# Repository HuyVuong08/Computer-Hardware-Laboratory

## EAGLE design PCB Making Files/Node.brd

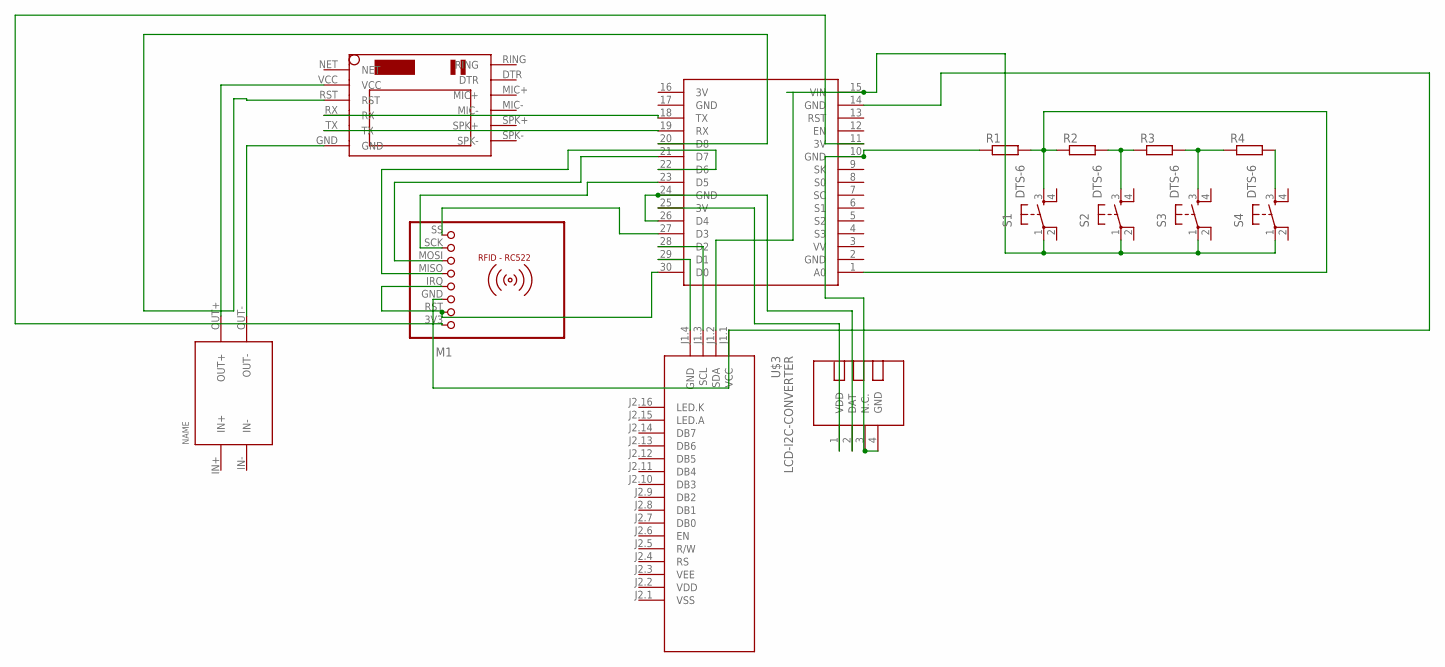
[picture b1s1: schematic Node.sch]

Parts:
M1: RFID-RC522
R1, R2, R3, R4: R-EU_0817/22; P0817/22
S1, S2, S3, S4: DTS-6
U$1: NODEMCU
U$2: TEMP-HUM-SENSOR-DHT11
U$3: LCD-I2C-CONVERTER
U$4: SIM800LMODULE
U$5: CP8-ADJ

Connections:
3V: U$1.16 (3V)
GND: U$1.2 (GND), U$1.17 (GND)
unnamed: U$4.GND, U$5.OUT-
unnamed: U$4.VCC, U$5.OUT+
unnamed: U$1.20 (D8), U$4.RST
unnamed: U$1.18 (TX), U$4.RX
unnamed: U$1.19 (RX), U$4.TX
unnamed: M1.MISO (5), U$1.22 (D6)
unnamed: M1.MOSI (6), U$1.21 (D7)
unnamed: M1.SCK (7), U$1.23 (D5)
unnamed: U$1.25 (3V), U$2.1 (VDD)
unnamed: M1.SS (8), U$1.27 (D3)
unnamed: U$1.24 (GND), U$1.26 (D4), U$2.2 (DAT)
unnamed: U$1.29 (D1), U$3.J1.4 (GND)
unnamed: U$1.28 (D2), U$3.J1.3 (SCL)
unnamed: M1.GND (3), U$1.14 (GND), U$3.J1.1 (VCC)
unnamed: R1.1, U$1.10 (GND), U$2.3 (N.C.), U$2.4 (GND)
unnamed: M1.IRQ (4), M1.RST (2), U$1.30 (D0)
unnamed: M1.3V3 (1), U$1.11 (3V)
unnamed: R1.2, R2.1, S1.3, U$1.1 (A0)
unnamed: R2.2, R3.1, S2.3
unnamed: R3.2, R4.1, S3.3
unnamed: R4.2, S4.3
unnamed: S1.1, S2.1, S3.1, S4.1, U$1.15 (VIN), U$3.J1.2 (SDA)

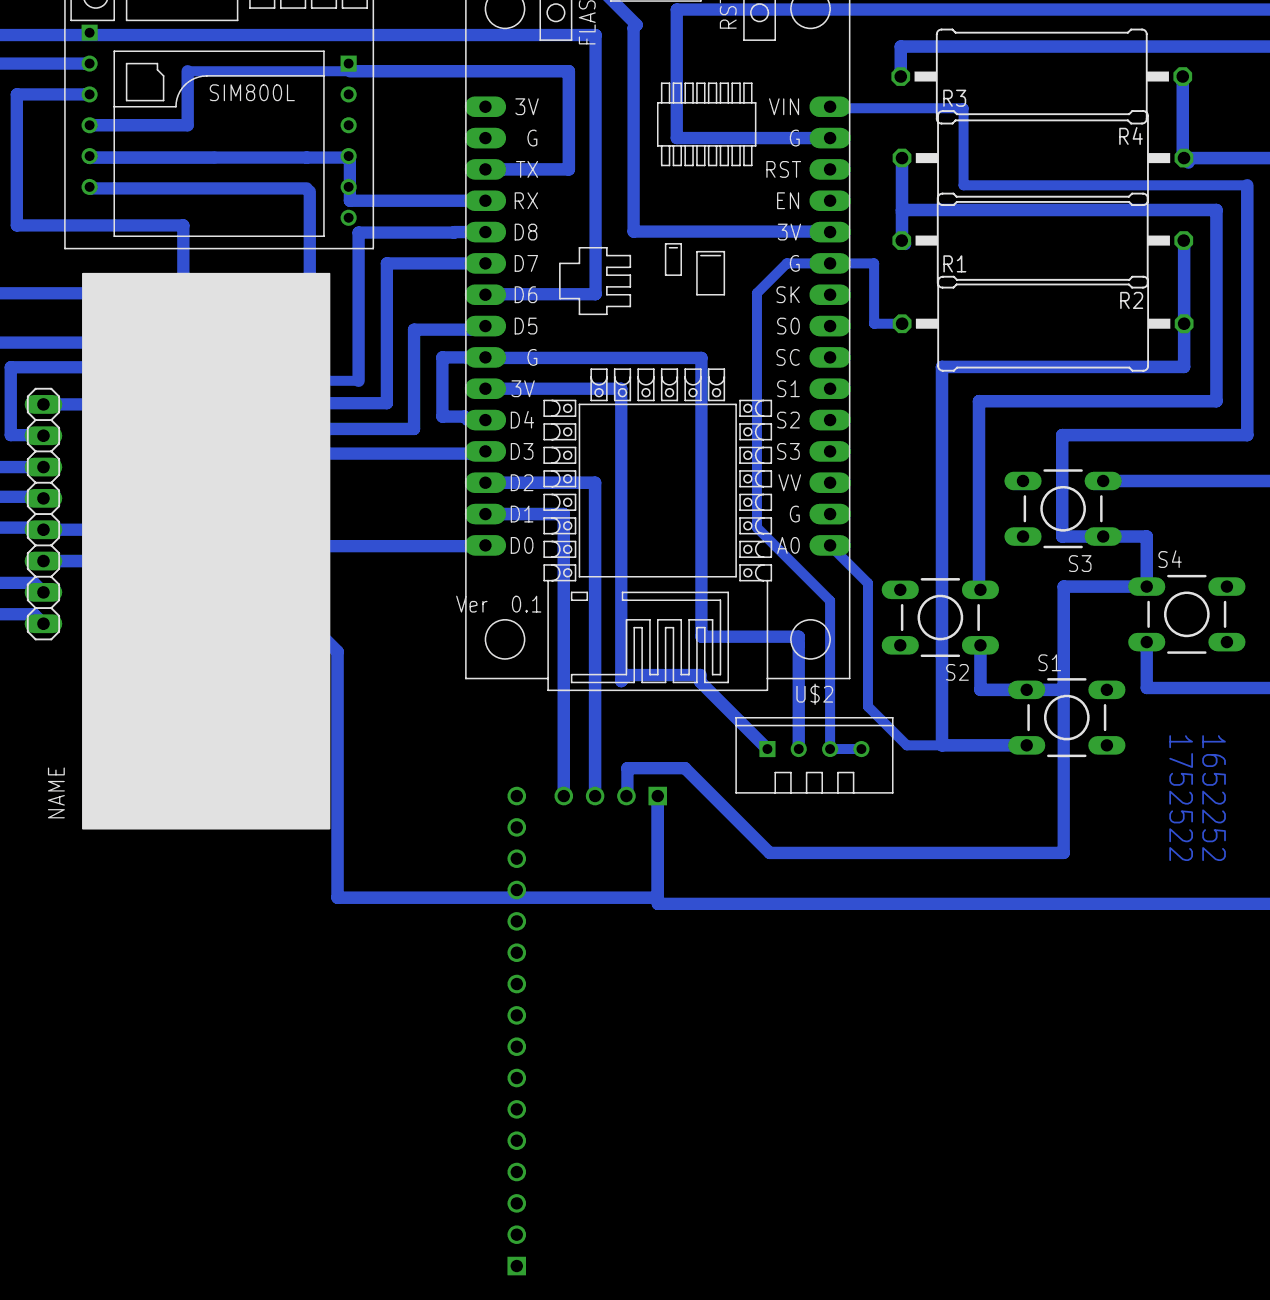
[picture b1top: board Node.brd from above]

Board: 2 copper layers, 14 parts (1 on the bottom side), 23 nets.

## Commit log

2019-05-26 Initialize SMART_HOME Project
2019-05-26 Rename
2019-05-26 Greeting State
2019-05-26 .vscode
2019-05-27 Remove Dublicated directory
2019-05-27 RFID
2019-05-27 Menu
2019-05-28 update DHT11
2019-05-29 LCD and Buttons
2019-05-29 LCD and Button
2019-05-29 Update Menu
2019-05-30 DHT11 Update
2019-05-31 RFID and DHT11
2019-06-02 SIM800L update
2019-06-04 SIM80L update
2019-06-04 Minor changes
2019-06-05 .vscode update
2019-06-05 Detele duplicated directory
2019-06-05 Matching components
2019-06-05 Registration System Matched
2019-06-06 Removing Dublicated directory
2019-06-06 Function Map
2019-06-06 Intergrating DHT11 into the System
2019-06-07 Intergating State Network Connection
2019-06-11 Problem with RFID
2019-06-11 First Attemp to fix RIFD
2019-06-12 Finishing up, RFID Problem Remaining
2019-06-12 Function Update
2019-06-16 SIM800L modification
2019-06-16 Little changes
2019-06-17 Update RFID Function
2019-06-17 Remove .vscode/ipch/*
2019-06-17 Modify RFID Funtionality
2019-06-17 RFID Modification
2019-06-17 Confict Fixed
2019-06-19 RFID Remake version 2.0
2019-06-19 RFID version 2.0. Implementing On_RFID_Verify
2019-06-19 Remove Redundant Files
2019-06-19 RFID.ino verion 2.0: Implementation Complete (LogIn, Register, CardDisprove).
2019-06-20 RFID.ino Finished
2019-06-20 Updating _RFID.ino
2019-06-22 Intergrating New Disprove Function to SMART_HOME
2019-06-22 Rerouting Program Flows
2019-06-22 All Done remaining untested RFID and SIM800L due to Equipment Shotages
2019-06-24 Final Update. Project Finished
2019-06-25 PCB Making
2019-06-25 Rename Folder

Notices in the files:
parts and their libraries:
diy-modules: Released under the Creative Commons Attribution 4.0 International License: http://creativecommons.org/licenses/by/4.0
